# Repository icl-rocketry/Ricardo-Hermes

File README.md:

# Hermes - ICLR Radio Gateway board

ESP32c3 + SX1280 + SKY66112-11 Half-Duplex Lora radio gateway board.

## WIP!

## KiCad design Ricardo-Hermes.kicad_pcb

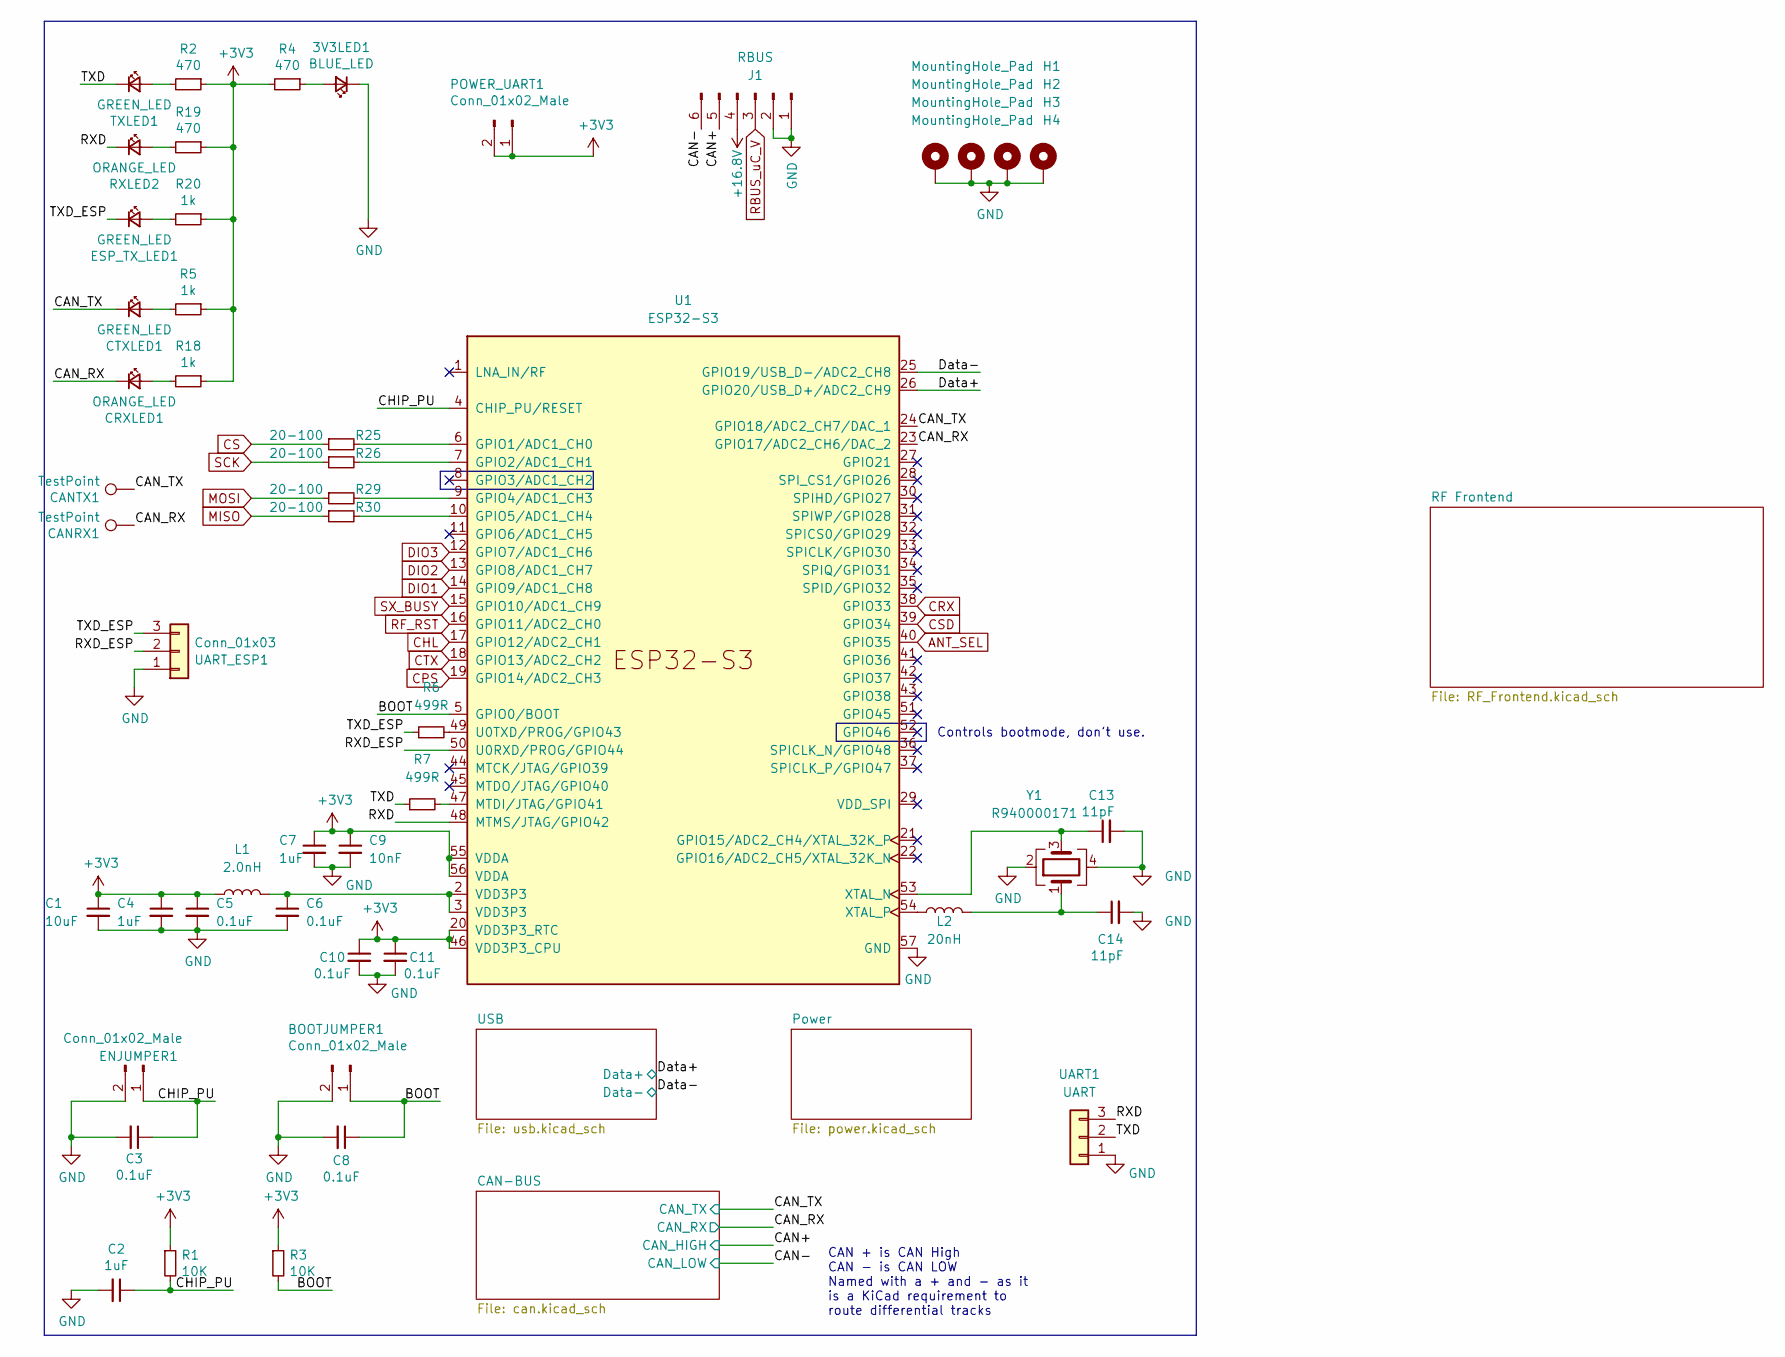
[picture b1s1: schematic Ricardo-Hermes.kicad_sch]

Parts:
3V3LED1: BLUE_LED; D_0402_1005Metric
BOOTJUMPER1: Conn_01x02_Male; PinHeader_1x02_P2.54mm_Vertical
C1: 10uF; C_0402_1005Metric
C2, C4, C7: 1uF; C_0402_1005Metric
C3, C5, C6, C8, C10, C11: 0.1uF; C_0402_1005Metric
C9: 10nF; C_0402_1005Metric
C13, C14: 11pF; C_0402_1005Metric
CANRX1: TestPoint; TestPoint_Pad_D1.0mm
CANTX1: TestPoint; TestPoint_Pad_D1.0mm
CRXLED1: ORANGE_LED; D_0402_1005Metric
CTXLED1: GREEN_LED; D_0402_1005Metric
ENJUMPER1: Conn_01x02_Male; PinHeader_1x02_P2.54mm_Vertical
ESP_TX_LED1: GREEN_LED; D_0402_1005Metric
H1, H2, H3, H4: MountingHole_Pad; MountingHole_3.2mm_M3_DIN965_Pad
J1: RBUS; Molex_Mini-Fit_Jr_5566-06A_2x03_P4.20mm_Vertical
L1: 2.0nH; L_0402_1005Metric
L2: 20nH; L_0402_1005Metric
POWER_UART1: Conn_01x02_Male; PinHeader_1x02_P2.54mm_Vertical
R1, R3: 10K; R_0402_1005Metric
R2, R4, R19: 470; R_0402_1005Metric
R5, R18, R20: 1k; R_0402_1005Metric
R6, R7: 499R; R_0402_1005Metric
R25, R26, R29, R30: 20-100; R_0402_1005Metric
RXLED2: ORANGE_LED; D_0402_1005Metric
TXLED1: GREEN_LED; D_0402_1005Metric
U1: ESP32-S3; QFN40P700X700X90-57N
UART1: UART; Molex_Nano-Fit_105313-xx03_1x03_P2.50mm_Horizontal
UART_ESP1: Conn_01x03; PinHeader_1x03_P2.54mm_Vertical
Y1: R940000171; Crystal_SMD_2016-4Pin_2.0x1.6mm

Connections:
+16.8V: J1.4
/BOOT: BOOTJUMPER1.1, C8.1, R3.2, U1.5 (GPIO0/BOOT)
/CAN+: J1.5; also elsewhere on the board
/CAN-: J1.6; also elsewhere on the board
/CAN_RX: CANRX1.1, CRXLED1.1 (K), U1.23 (GPIO17/ADC2_CH6/DAC_2); also elsewhere on the board
/CAN_TX: CANTX1.1, CTXLED1.1 (K), U1.24 (GPIO18/ADC2_CH7/DAC_1); also elsewhere on the board
/CHIP_PU: C2.1, C3.1, ENJUMPER1.1, R1.2, U1.4 (CHIP_PU/RESET)
/Data+: U1.26 (GPIO20/USB_D+/ADC2_CH9); also elsewhere on the board
/Data-: U1.25 (GPIO19/USB_D-/ADC2_CH8); also elsewhere on the board
/RXD: RXLED2.1 (K), U1.48 (MTMS/JTAG/GPIO42), UART1.3
/RXD_ESP: U1.50 (U0RXD/PROG/GPIO44), UART_ESP1.2
/TXD: R7.1, TXLED1.1 (K), UART1.2
/TXD_ESP: ESP_TX_LED1.1 (K), R6.1, UART_ESP1.3
ANT_SEL: U1.40 (GPIO35); also elsewhere on the board
CHL: U1.17 (GPIO12/ADC2_CH1); also elsewhere on the board
CPS: U1.19 (GPIO14/ADC2_CH3); also elsewhere on the board
CRX: U1.38 (GPIO33); also elsewhere on the board
CS: R25.1; also elsewhere on the board
CSD: U1.39 (GPIO34); also elsewhere on the board
CTX: U1.18 (GPIO13/ADC2_CH2); also elsewhere on the board
DIO1: U1.14 (GPIO9/ADC1_CH8); also elsewhere on the board
DIO2: U1.13 (GPIO8/ADC1_CH7); also elsewhere on the board
DIO3: U1.12 (GPIO7/ADC1_CH6); also elsewhere on the board
GND: 3V3LED1.1 (K), BOOTJUMPER1.2, C1.2, C2.2, C3.2, C4.2, C5.2, C6.2, C7.2, C8.2, C9.2, C10.2, C11.2, C13.2, C14.2, ENJUMPER1.2, H1.1, H2.1, H3.1, H4.1, J1.1, J1.2, U1.57 (GND), UART1.1, UART_ESP1.1, Y1.2, Y1.4; also elsewhere on the board
MISO: R30.1; also elsewhere on the board
MOSI: R29.1; also elsewhere on the board
unnamed: 3V3LED1.2 (A), R4.1
unnamed: C6.1, L1.2, U1.2 (VDD3P3), U1.3 (VDD3P3)
unnamed: C14.1, L2.2, Y1.1
unnamed: CRXLED1.2 (A), R18.2
unnamed: CTXLED1.2 (A), R5.2
unnamed: ESP_TX_LED1.2 (A), R20.2
unnamed: R19.2, RXLED2.2 (A)
unnamed: R2.2, TXLED1.2 (A)
unnamed: R25.2, U1.6 (GPIO1/ADC1_CH0)
unnamed: R26.2, U1.7 (GPIO2/ADC1_CH1)
unnamed: R29.2, U1.9 (GPIO4/ADC1_CH3)
unnamed: R30.2, U1.10 (GPIO5/ADC1_CH4)
unnamed: R7.2, U1.47 (MTDI/JTAG/GPIO41)
unnamed: R6.2, U1.49 (U0TXD/PROG/GPIO43)
unnamed: C13.1, U1.53 (XTAL_N), Y1.3
unnamed: L2.1, U1.54 (XTAL_P)
RBUS_uC_V: J1.3; also elsewhere on the board
RF_RST: U1.16 (GPIO11/ADC2_CH0); also elsewhere on the board
SCK: R26.1; also elsewhere on the board
SX_BUSY: U1.15 (GPIO10/ADC1_CH9); also elsewhere on the board

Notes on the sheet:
Controls bootmode, don't use.
CAN + is CAN High CAN - is CAN LOW Named with a + and - as it is a KiCad requirement to route differential tracks

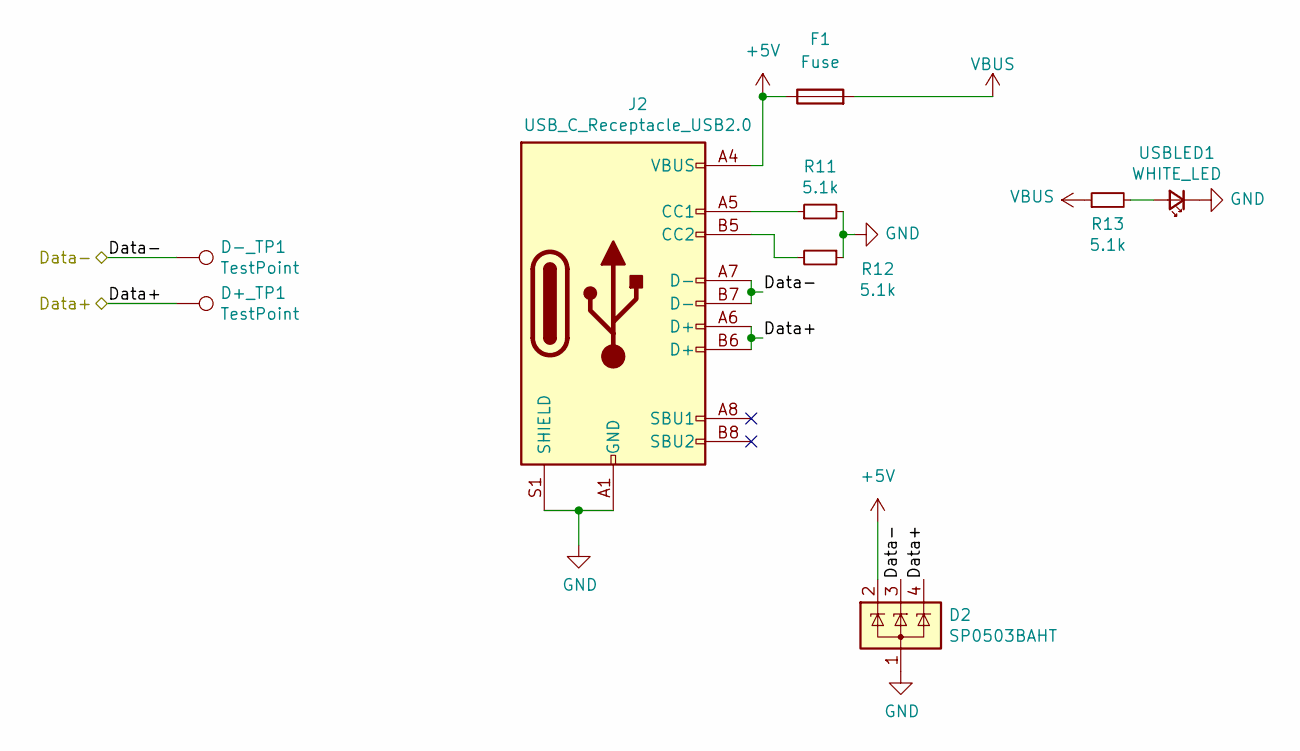
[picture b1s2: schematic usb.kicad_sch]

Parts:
D2: SP0503BAHT; SOT-143
D+_TP1: TestPoint; TestPoint_Pad_D1.0mm
D-_TP1: TestPoint; TestPoint_Pad_D1.0mm
F1: Fuse; Fuse_0603_1608Metric
J2: USB_C_Receptacle_USB2.0; USB_C_Receptacle_Palconn_UTC16-G
R11, R12, R13: 5.1k; R_0402_1005Metric
USBLED1: WHITE_LED; D_0402_1005Metric

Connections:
+5V: D2.2 (K), F1.1, J2.A4 (VBUS), J2.A9 (VBUS), J2.B4 (VBUS), J2.B9 (VBUS)
/Data+: D2.4 (K), D+_TP1.1, J2.A6 (D+), J2.B6 (D+); also elsewhere on the board
/Data-: D2.3 (K), D-_TP1.1, J2.A7 (D-), J2.B7 (D-); also elsewhere on the board
GND: D2.1 (A), J2.A1 (GND), J2.A12 (GND), J2.B1 (GND), J2.B12 (GND), J2.S1 (SHIELD), R11.2, R12.1, USBLED1.1 (K); also elsewhere on the board
unnamed: J2.A5 (CC1), R11.1
unnamed: J2.B5 (CC2), R12.2
unnamed: R13.2, USBLED1.2 (A)
VBUS: F1.2, R13.1; also elsewhere on the board

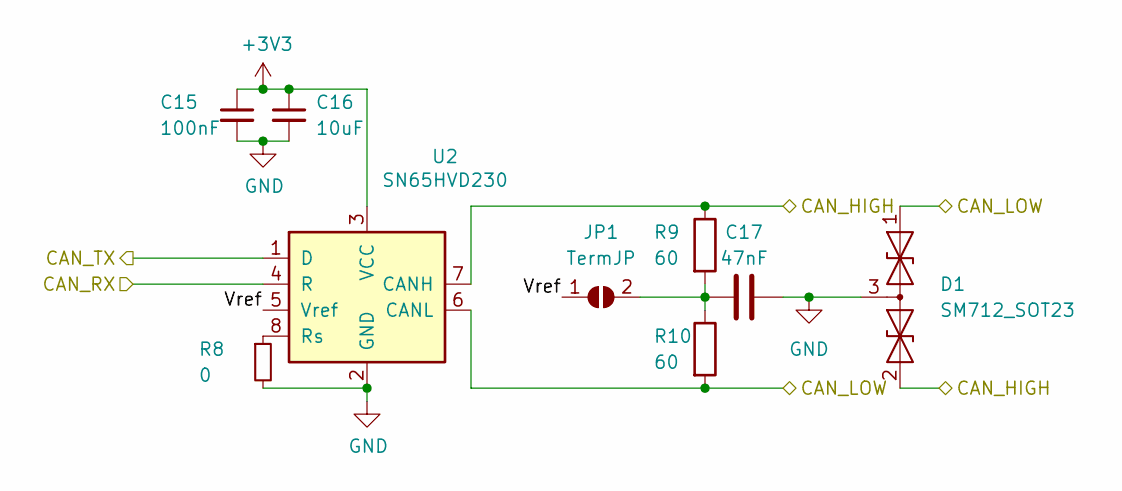
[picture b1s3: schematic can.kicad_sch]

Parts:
C15: 100nF; C_0402_1005Metric
C16: 10uF; C_0402_1005Metric
C17: 47nF; C_0402_1005Metric
D1: SM712_SOT23; SOT-23
JP1: TermJP; SolderJumper-2_P1.3mm_Open_RoundedPad1.0x1.5mm
R8: 0; R_0603_1608Metric
R9, R10: 60; R_0603_1608Metric
U2: SN65HVD230; SOIC-8_3.9x4.9mm_P1.27mm

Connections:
/CAN+: D1.2 (A2), R9.1, U2.7 (CANH); also elsewhere on the board
/CAN-: D1.1 (A1), R10.2, U2.6 (CANL); also elsewhere on the board
/CAN-BUS/Vref: JP1.1 (A), U2.5 (Vref)
/CAN_RX: U2.4 (R); also elsewhere on the board
/CAN_TX: U2.1 (D); also elsewhere on the board
GND: C15.2, C16.2, C17.2, D1.3 (common), R8.2, U2.2 (GND); also elsewhere on the board
unnamed: C17.1, JP1.2 (B), R9.2, R10.1
unnamed: R8.1, U2.8 (Rs)

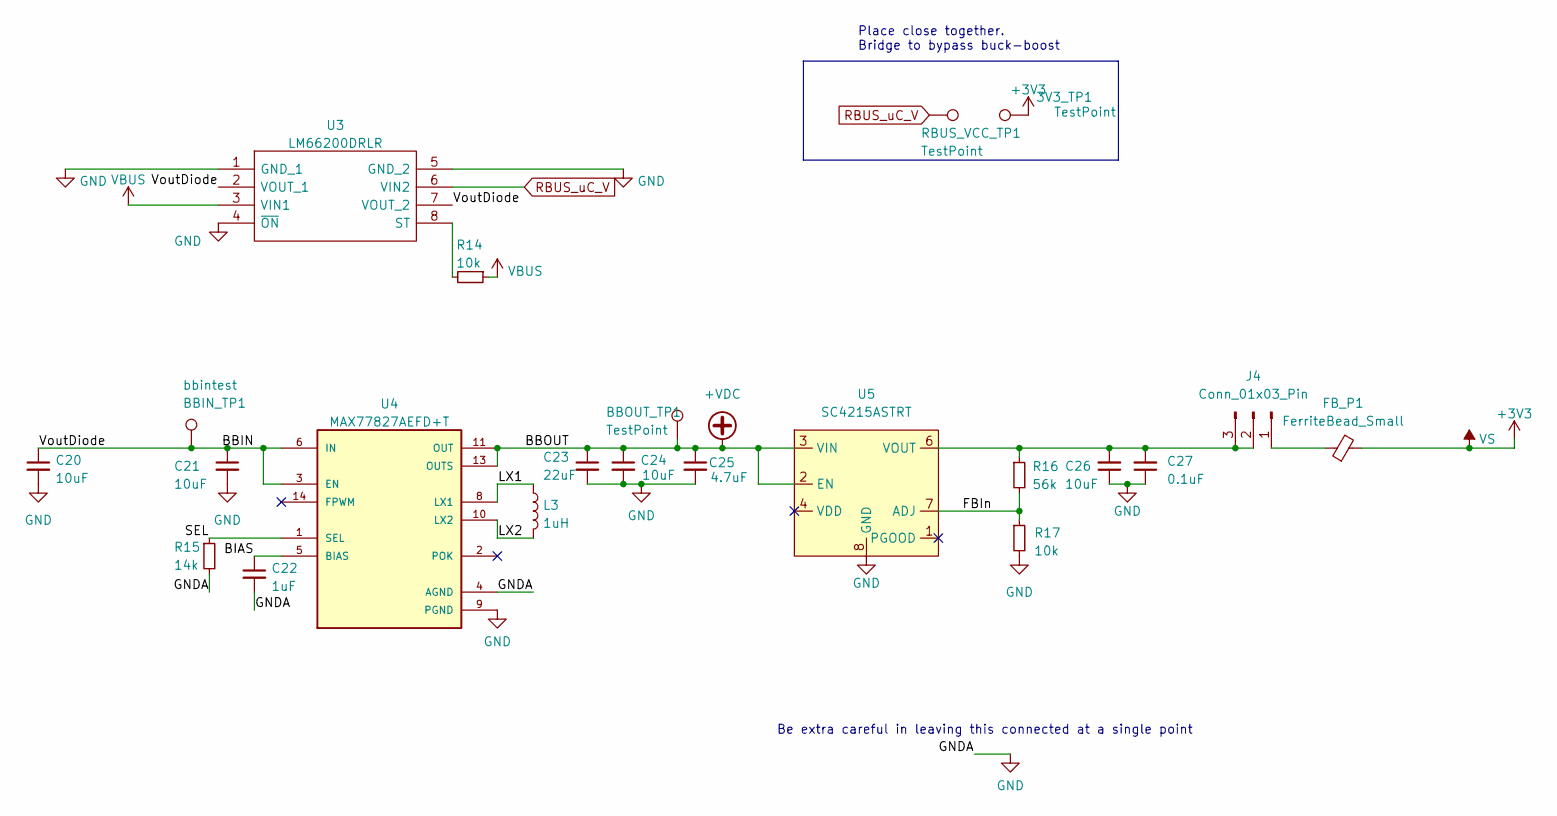
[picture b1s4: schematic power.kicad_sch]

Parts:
3V3_TP1: TestPoint; TestPoint_Pad_D1.5mm
BBIN_TP1: bbintest; TestPoint_Pad_D1.5mm
BBOUT_TP1: TestPoint; TestPoint_Pad_D1.5mm
C20, C24, C26: 10uF; C_0402_1005Metric
C21: 10uF; C_0603_1608Metric
C22: 1uF; C_0402_1005Metric
C23: 22uF; C_0603_1608Metric
C25: 4.7uF; C_0402_1005Metric
C27: 0.1uF; C_0402_1005Metric
FB_P1: FerriteBead_Small; L_0603_1608Metric
J4: Conn_01x03_Pin; PinHeader_1x03_P2.54mm_Vertical
L3: 1uH; L_0805_2012Metric
R14, R17: 10k; R_0402_1005Metric
R15: 14k; R_0402_1005Metric
R16: 56k; R_0402_1005Metric
RBUS_VCC_TP1: TestPoint; TestPoint_Pad_D1.5mm
U3: LM66200DRLR; SOTFL50P160X60-8N; Manufacturer_Part_Number LM66200DRLR; Mouser Part Number 595-LM66200DRLR
U4: MAX77827AEFD+T; CONV_MAX77827AEFD+T; PARTREV B
U5: SC4215ASTRT; SOIC127P599X175-9N

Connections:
+VDC: BBOUT_TP1.1, C23.1, C24.1, C25.1, U4.11 (OUT), U4.13 (OUTS), U5.2 (EN), U5.3 (VIN)
/Power/BBIN: BBIN_TP1.1, C20.1, C21.1, U3.2 (VOUT_1), U3.7 (VOUT_2), U4.3 (EN), U4.6 (IN)
/Power/BIAS: C22.1, U4.5 (BIAS)
/Power/FBIn: R16.2, R17.1, U5.7 (ADJ)
/Power/LX1: L3.1, U4.8 (LX1)
/Power/LX2: L3.2, U4.10 (LX2)
/Power/SEL: R15.1, U4.1 (SEL)
GND: C20.2, C21.2, C22.2, C23.2, C24.2, C25.2, C26.1, C27.1, R15.2, R17.2, U3.1 (GND_1), U3.4 (~ON), U3.5 (GND_2), U4.4 (AGND), U4.9 (PGND), U5.8 (GND), U5.9 (GND); also elsewhere on the board
unnamed: R14.2, U3.8 (ST)
RBUS_uC_V: RBUS_VCC_TP1.1, U3.6 (VIN2); also elsewhere on the board
VBUS: R14.1, U3.3 (VIN1); also elsewhere on the board

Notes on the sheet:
Place close together. Bridge to bypass buck-boost
Be extra careful in leaving this connected at a single point

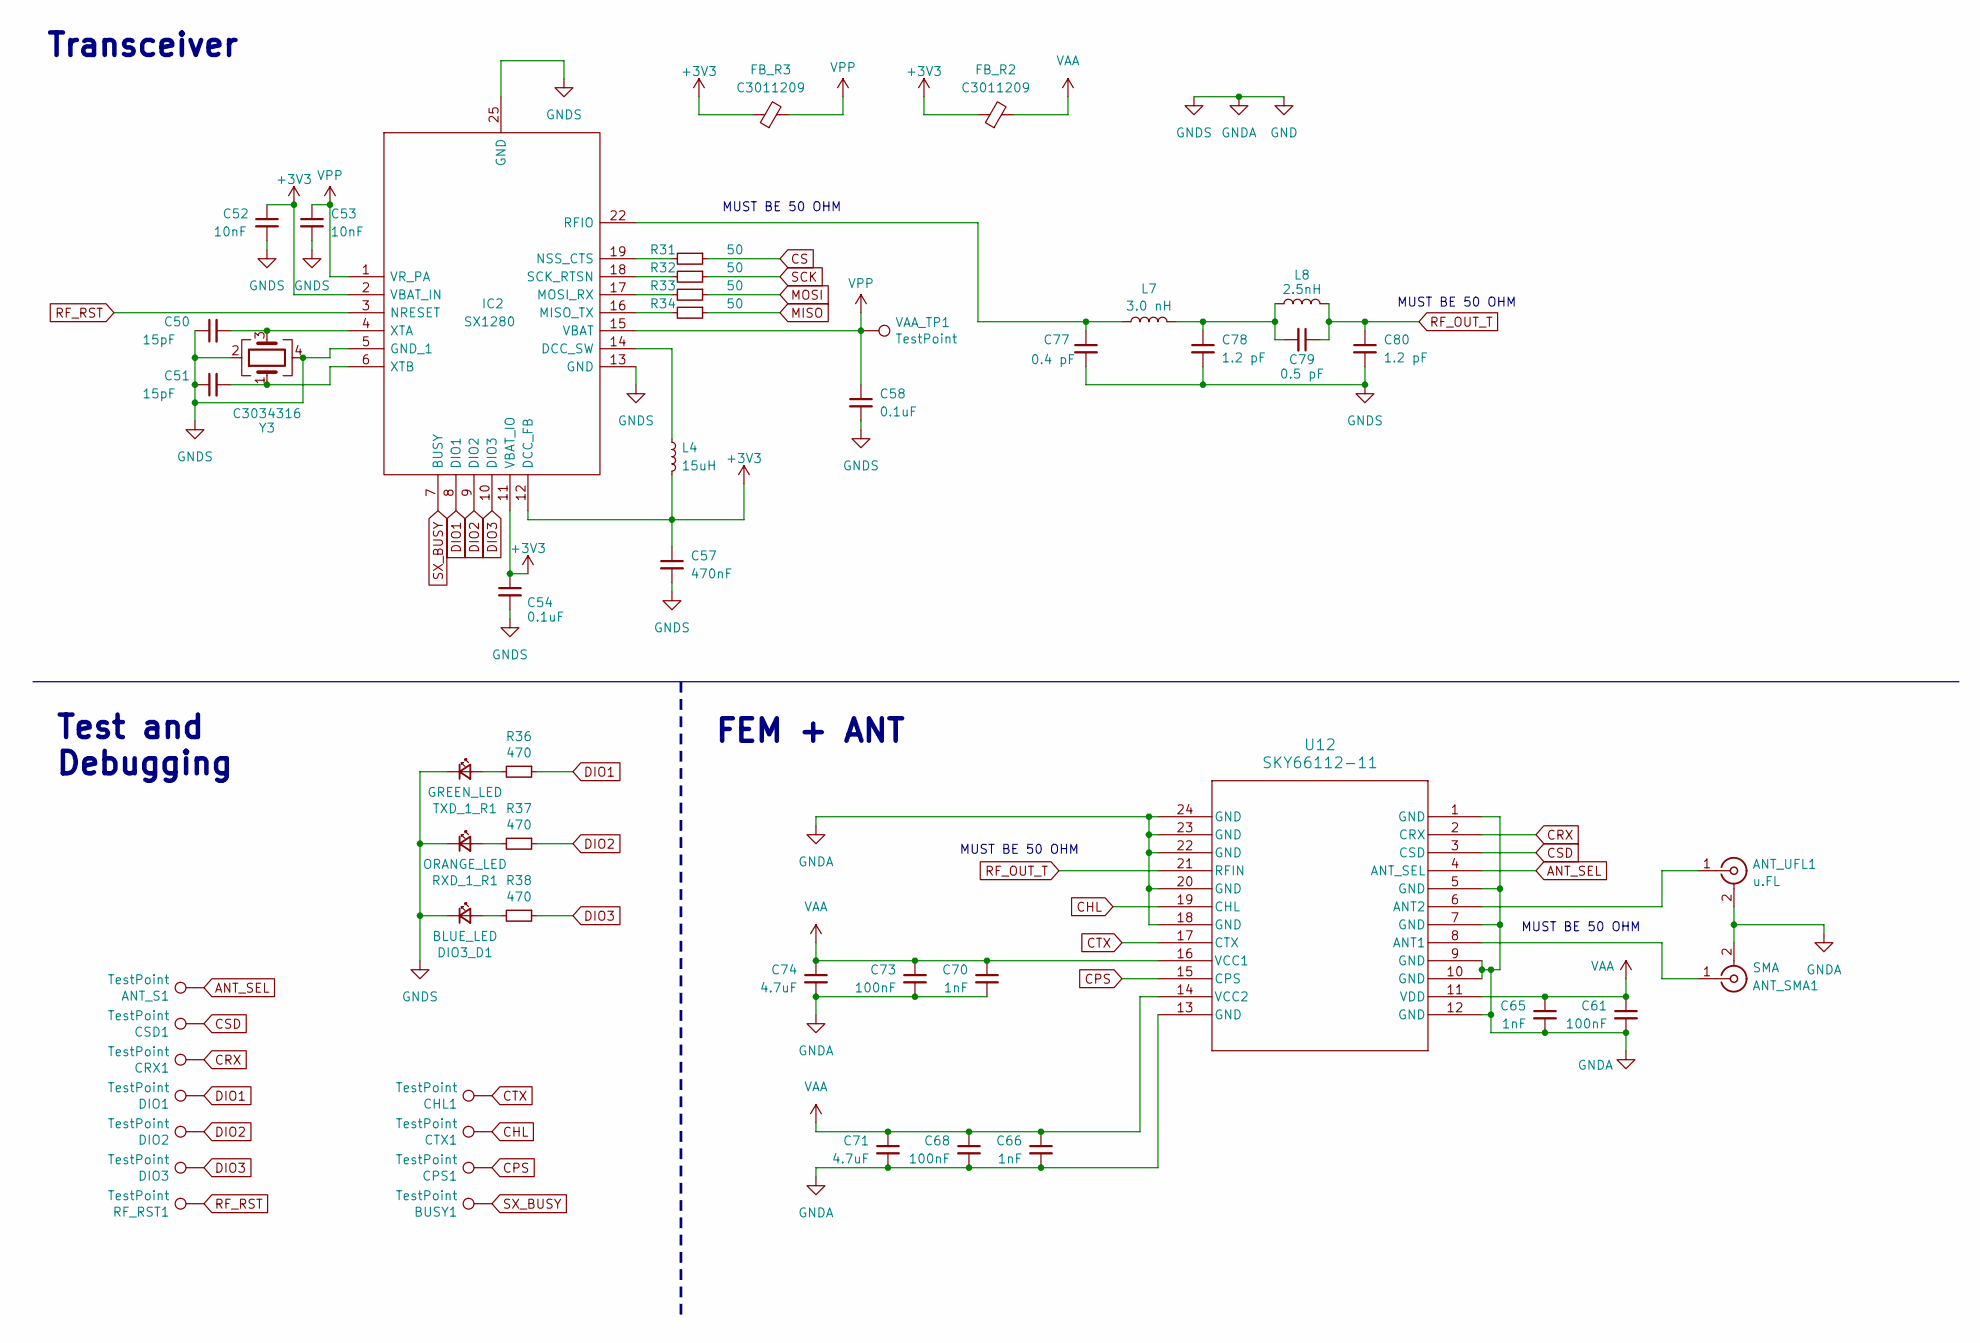
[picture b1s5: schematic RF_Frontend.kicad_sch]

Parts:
ANT_S1: TestPoint; TestPoint_Pad_D1.0mm
ANT_SMA1: SMA; SMA_Molex_73251-1153_EdgeMount_Horizontal
ANT_UFL1: u.FL; U.FL_Hirose_U.FL-R-SMT-1_Vertical
BUSY1: TestPoint; TestPoint_Pad_D1.0mm
C50, C51: 15pF; C_0402_1005Metric
C52, C53: 10nF; C_0402_1005Metric
C54, C58: 0.1uF; C_0402_1005Metric
C57: 470nF; C_0402_1005Metric
C61, C68, C73: 100nF; C_0402_1005Metric
C65, C66, C70: 1nF; C_0402_1005Metric
C71, C74: 4.7uF; C_0603_1608Metric
C77: 0.4 pF; C_0402_1005Metric
C78, C80: 1.2 pF; C_0402_1005Metric
C79: 0.5 pF; C_0402_1005Metric
CHL1: TestPoint; TestPoint_Pad_D1.0mm
CPS1: TestPoint; TestPoint_Pad_D1.0mm
CRX1: TestPoint; TestPoint_Pad_D1.0mm
CSD1: TestPoint; TestPoint_Pad_D1.0mm
CTX1: TestPoint; TestPoint_Pad_D1.0mm
DIO1, DIO2, DIO3: TestPoint; TestPoint_Pad_D1.0mm
DIO3_D1: BLUE_LED; D_0402_1005Metric
FB_R2, FB_R3: C3011209; L_0603_1608Metric
IC2: SX1280; QFN50P400X400X95-24N; Manufacturer_Part_Number SX1280IMLTRT; Mouser Part Number 947-SX1280IMLTRT
L4: 15uH; L_0603_1608Metric
L7: 3.0 nH; L_0402_1005Metric
L8: 2.5nH; L_0402_1005Metric
R31, R32, R33, R34: 50; R_0402_1005Metric
R36, R37, R38: 470; R_0402_1005Metric
RF_RST1: TestPoint; TestPoint_Pad_D1.0mm
RXD_1_R1: ORANGE_LED; D_0402_1005Metric
TXD_1_R1: GREEN_LED; D_0402_1005Metric
U12: SKY66112-11; SKY66112-11_SKY
VAA_TP1: TestPoint; TestPoint_Pad_D1.0mm
Y3: C3034316; Crystal_SMD_2016-4Pin_2.0x1.6mm

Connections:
ANT_SEL: ANT_S1.1, U12.4 (ANT_SEL); also elsewhere on the board
CHL: CTX1.1, U12.19 (CHL); also elsewhere on the board
CPS: CPS1.1, U12.15 (CPS); also elsewhere on the board
CRX: CRX1.1, U12.2 (CRX); also elsewhere on the board
CS: R31.1; also elsewhere on the board
CSD: CSD1.1, U12.3 (CSD); also elsewhere on the board
CTX: CHL1.1, U12.17 (CTX); also elsewhere on the board
DIO1: DIO1.1, IC2.8 (DIO1), R36.1; also elsewhere on the board
DIO2: DIO2.1, IC2.9 (DIO2), R37.1; also elsewhere on the board
DIO3: DIO3.1, IC2.10 (DIO3), R38.1; also elsewhere on the board
GND: ANT_SMA1.2 (Ext), ANT_UFL1.2 (Ext), C50.1, C51.1, C52.2, C53.2, C54.2, C57.2, C58.2, C61.2, C65.2, C66.2, C68.2, C70.2, C71.2, C73.2, C74.2, C77.2, C78.2, C80.2, DIO3_D1.1 (K), IC2.5 (GND_1), IC2.13 (GND), IC2.20 (GND), IC2.21 (GND), IC2.23 (GND), IC2.24 (GND), IC2.25 (GND), RXD_1_R1.1 (K), TXD_1_R1.1 (K), U12.1 (GND), U12.5 (GND), U12.7 (GND), U12.9 (GND), U12.10 (GND), U12.12 (GND), U12.13 (GND), U12.18 (GND), U12.20 (GND), U12.22 (GND), U12.23 (GND), U12.24 (GND), Y3.2, Y3.4; also elsewhere on the board
MISO: R34.1; also elsewhere on the board
MOSI: R33.1; also elsewhere on the board
unnamed: ANT_SMA1.1 (In), U12.8 (ANT1)
unnamed: ANT_UFL1.1 (In), U12.6 (ANT2)
unnamed: C78.1, C79.2, L7.2, L8.1
unnamed: DIO3_D1.2 (A), R38.2
unnamed: IC2.16 (MISO_TX), R34.2
unnamed: IC2.17 (MOSI_RX), R33.2
unnamed: IC2.19 (NSS_CTS), R31.2
unnamed: C77.1, IC2.22 (RFIO), L7.1
unnamed: IC2.18 (SCK_RTSN), R32.2
unnamed: C50.2, IC2.4 (XTA), Y3.3
unnamed: C51.2, IC2.6 (XTB), Y3.1
unnamed: IC2.14 (DCC_SW), L4.1
unnamed: R37.2, RXD_1_R1.2 (A)
unnamed: R36.2, TXD_1_R1.2 (A)
RF_OUT_T: C79.1, C80.1, L8.2, U12.21 (RFIN)
RF_RST: IC2.3 (NRESET), RF_RST1.1; also elsewhere on the board
SCK: R32.1; also elsewhere on the board
SX_BUSY: BUSY1.1, IC2.7 (BUSY); also elsewhere on the board
VAA: C61.1, C65.1, C66.1, C68.1, C70.1, C71.1, C73.1, C74.1, FB_R2.2, U12.11 (VDD), U12.14 (VCC2), U12.16 (VCC1)

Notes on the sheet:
MUST BE 50 OHM
Transceiver
Test and Debugging
FEM + ANT

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
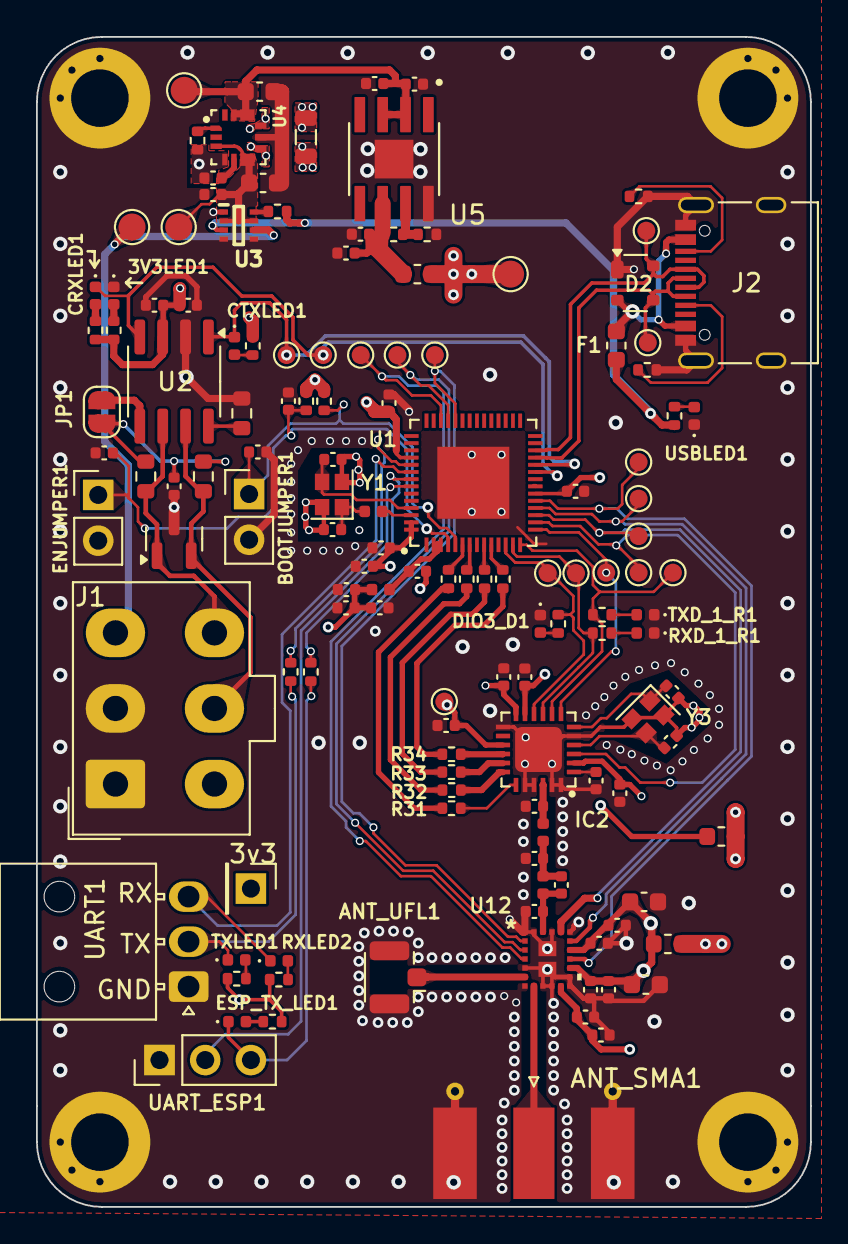
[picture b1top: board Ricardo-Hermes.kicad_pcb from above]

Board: 4 copper layers, 43.0 x 65.0 mm, 138 parts (0 on the bottom side), 81 nets.

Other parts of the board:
3v3: Conn_01x02_Male; PinHeader_1x01_P2.54mm_Vertical

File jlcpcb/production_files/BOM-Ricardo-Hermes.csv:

Comment,Designator,Footprint,LCSC,Quantity
MAX77827AEFD+T,U4,CONV_MAX77827AEFD+T,C1020009,1
1uH,L3,L_0805_2012Metric,C113100,1
470,"R2,R36,R37,R38,R4",R_0402_1005Metric,C114877,5
1k,"R18,R20,R5",R_0402_1005Metric,C11702,3
SN65HVD230,U2,SOIC-8_3.9x4.9mm_P1.27mm,C12084,1
SX1280,IC2,QFN50P400X400X95-24N,C125969,1
ORANGE_LED,CRXLED1,D_0402_1005Metric,C130720,1
GREEN_LED,CTXLED1,D_0402_1005Metric,C130722,1
BLUE_LED,"3V3LED1,DIO3_D1",D_0402_1005Metric,C130724,2
WHITE_LED,USBLED1,D_0402_1005Metric,C130725,1
Fuse,F1,Fuse_0603_1608Metric,C135323,1
499R,"R6,R7",R_0402_1005Metric,C137970,2
1nF,"C65,C66,C70",C_0402_1005Metric,C14442,3
1uF,"C2,C22,C4,C7",C_0402_1005Metric,C14445,4
10nF,"C52,C53,C9",C_0402_1005Metric,C15195,3
15uH,L4,L_0603_1608Metric,C18221256,1
4.7uF,"C71,C74",C_0603_1608Metric,C19666,2
470,R19,R_0402_1005Metric,C25117,1
0,R8,R_0603_1608Metric,C253507,1
10k,"R14,R17",R_0402_1005Metric,C25744,2
56k,R16,R_0402_1005Metric,C25796,1
5.1k,"R11,R12,R13",R_0402_1005Metric,C25905,3
SKY66112-11,U12,SKY66112-11_SKY,C2654460,1
3.0 nH,L7,L_0402_1005Metric,C275284,1
ESP32-S3,U1,QFN40P700X700X90-57N,C2913192,1
USB_C_Receptacle_USB2.0,J2,USB_C_Receptacle_Palconn_UTC16-G,C2988369,1
FerriteBead_Small,"FB_P1,FB_R2,FB_R3",L_0603_1608Metric,C3011209,3
C3034316,Y3,Crystal_SMD_2016-4Pin_2.0x1.6mm,C3034316,1
2.5nH,L8,L_0402_1005Metric,C317668,1
20nH,L2,L_0402_1005Metric,C317958,1
LM66200DRLR,U3,SOTFL50P160X60-8N,C3235556,1
SC4215ASTRT,U5,SOIC127P599X175-9N,C353859,1
15pF,C50,C_0402_1005Metric,C441742,1
470nF,C57,C_0402_1005Metric,C47339,1
SM712_SOT23,D1,SOT-23,C502564,1
14k,R15,R_0402_1005Metric,C54831,1
4.7uF,C25,C_0402_1005Metric,C5718982,1
22uF,C23,C_0603_1608Metric,C60077,1
10K,"R1,R3",R_0402_1005Metric,C60490,2
SP0503BAHT,D2,SOT-143,C7074,1
11pF,"C13,C14",C_0402_1005Metric,C710643,2
R940000171,Y1,Crystal_SMD_2016-4Pin_2.0x1.6mm,C7420784,1
2.0nH,L1,L_0402_1005Metric,C76769,1
1.2 pF,"C78,C80",C_0402_1005Metric,C76899,2
0.5 pF,C79,C_0402_1005Metric,C76911,1
15pF,C51,C_0402_1005Metric,C76950,1
10uF,"C1,C16,C20,C24,C26",C_0402_1005Metric,C77000,5
47nF,C17,C_0402_1005Metric,C77012,1
0.1uF,"C10,C11,C15,C27,C3,C5,C54,C58,C6,C61,C68,C73,C8",C_0402_1005Metric,C77020,13
20-100,"R25,R26,R29,R30,R31,R32,R33,R34",R_0402_1005Metric,C853312,8
10uF,C21,C_0603_1608Metric,C86275,1
u.FL,ANT_UFL1,U.FL_Hirose_U.FL-R-SMT-1_Vertical,C88374,1
0.4 pF,C77,C_0402_1005Metric,C88900,1
TestPoint,RF_RST1,TestPoint_Pad_D1.0mm,,1
RBUS,J1,Molex_Mini-Fit_Jr_5566-06A_2x03_P4.20mm_Vertical,,1
bbintest,BBIN_TP1,TestPoint_Pad_D1.5mm,,1
TestPoint,CRX1,TestPoint_Pad_D1.0mm,,1
60,R9,R_0603_1608Metric,,1
TestPoint,CSD1,TestPoint_Pad_D1.0mm,,1
TestPoint,CANRX1,TestPoint_Pad_D1.0mm,,1
TestPoint,DIO3,TestPoint_Pad_D1.0mm,,1
TestPoint,VAA_TP1,TestPoint_Pad_D1.0mm,,1
TestPoint,CTX1,TestPoint_Pad_D1.0mm,,1
SMA,ANT_SMA1,SMA_Molex_73251-1153_EdgeMount_Horizontal,,1
TermJP,JP1,SolderJumper-2_P1.3mm_Open_RoundedPad1.0x1.5mm,,1
TestPoint,CPS1,TestPoint_Pad_D1.0mm,,1
TestPoint,3V3_TP1,TestPoint_Pad_D1.5mm,,1
MountingHole_Pad,H3,MountingHole_3.2mm_M3_DIN965_Pad,,1
TestPoint,RBUS_VCC_TP1,TestPoint_Pad_D1.5mm,,1
TestPoint,BBOUT_TP1,TestPoint_Pad_D1.5mm,,1
UART,UART1,Molex_Nano-Fit_105313-xx03_1x03_P2.50mm_Horizontal,,1
TestPoint,CHL1,TestPoint_Pad_D1.0mm,,1
MountingHole_Pad,H1,MountingHole_3.2mm_M3_DIN965_Pad,,1
MountingHole_Pad,H4,MountingHole_3.2mm_M3_DIN965_Pad,,1
TestPoint,DIO1,TestPoint_Pad_D1.0mm,,1
Conn_01x02_Male,ENJUMPER1,PinHeader_1x02_P2.54mm_Vertical,,1
TestPoint,BUSY1,TestPoint_Pad_D1.0mm,,1
Conn_01x02_Male,BOOTJUMPER1,PinHeader_1x02_P2.54mm_Vertical,,1
TestPoint,ANT_S1,TestPoint_Pad_D1.0mm,,1
TestPoint,DIO2,TestPoint_Pad_D1.0mm,,1
TestPoint,CANTX1,TestPoint_Pad_D1.0mm,,1
MountingHole_Pad,H2,MountingHole_3.2mm_M3_DIN965_Pad,,1
60,R10,R_0603_1608Metric,,1
Conn_01x03,UART_ESP1,PinHeader_1x03_P2.54mm_Vertical,,1
Conn_01x02_Male,3v3,PinHeader_1x01_P2.54mm_Vertical,,1

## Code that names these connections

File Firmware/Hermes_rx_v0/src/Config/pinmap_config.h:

/*
**********************
* PINS               *
**********************
*/
#pragma once

namespace PinMap
{

    static constexpr int H_MISO = 12;
    static constexpr int H_MOSI = 13;
    static constexpr int H_SCLK = 14;

    static constexpr int MagCs = 15;
    static constexpr int ImuCs_1 = 16;
    static constexpr int ImuCs_2 = 17;

    // static constexpr int V_SCLK = 18;
    // static constexpr int V_MISO = 19;
    static constexpr int _SDA = 21;
    static constexpr int _SCL = 22;
    // static constexpr int V_MOSI = 23;

    static constexpr int V_SCLK = 37;
    static constexpr int V_MISO = 38;
    static constexpr int V_MOSI = 36;
    static constexpr int sdcs = 4;

    // static constexpr int SdCs_1 = 25;
    // static constexpr int SdCs_2 = 26;
    // static constexpr int Buzzer = 27;

    static constexpr int TxCan = 32;
    static constexpr int RxCan = 33;

    // AMP

    /*
    Pin means amp pin itself
     Mode | Description               | CSD (Pin 3) | CPS (Pin 15) | CRX (Pin 2) | CTX (Pin 17) | CHL (Pin 19)
     -----+---------------------------+-------------+--------------+-------------+--------------+-------------
     0    | All off (sleep mode)      | 0           | X            | X           | X            | X
     1    | Receive LNA mode          | 1           | 0            | 1           | 0            | X
     2    | Transmit high-power mode  | 1           | 0            | X           | 1            | 1
     3    | Transmit low-power mode   | 1           | 0            | X           | 1            | 0
     4    | Receive bypass mode       | 1           | 1            | 1           | 0            | X
     5    | Transmit bypass mode      | 1           | 1            | X           | 1            | X
     6    | All off (sleep mode)      | 1           | X            | 0           | 0            | X
    */
    static constexpr int AMP_ANT_SEL = 35; // 0 is SMA, 1 is UFL
    static constexpr int AMP_CSD = 34;     // AMP off (sleeping) -> 0, AMP on -> 1
    static constexpr int AMP_CRX = 33;     // Enable RX
    static constexpr int AMP_CHL = 17;     // high power TX -> 1, Low power TX -> 0
    static constexpr int AMP_CTX = 13;     // Enable TX
    static constexpr int AMP_CPS = 14;     // Bypass mode

    // SX1280
    static constexpr int SPI_SX1280_CS = 1;
    static constexpr int SPI_SX1280_SCK = 2;
    static constexpr int SPI_SX1280_MOSI = 4;
    static constexpr int SPI_SX1280_MISO = 5;
    static constexpr int SX1280_DIO1 = 9; // txd led
    static constexpr int SX1280_DIO2 = 8; // rxd led
    static constexpr int SX1280_DIO3 = 7;
    static constexpr int SX1280_BUSY = 10;
    static constexpr int SX1280_RST = 11;

    // UART
    static constexpr int TXD_ESP_UART = 43;
    static constexpr int RXD_ESP_UART = 44;
    static constexpr int TXD_UART = 41;
    static constexpr int RXD_UART = 42;

    // Pickle
    static constexpr int LoraReset = 11;
    static constexpr int LoraCs = 1;
    // might switch to busy, who knows lol
    static constexpr int LoraInt = 9;
    // static constexpr int TxCan = 27;
    // static constexpr int RxCan = 14;

    // static constexpr int TxCan = 33;
    // static constexpr int RxCan = 32;
    // static constexpr int SdDet_1 = 34;
    // static constexpr int SdDet_2 = 35;
    // static constexpr int BattVolt = 36;
    // static constexpr int LoraInt = 39;
};

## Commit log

2024-11-24 Alpha revision
2024-11-24 Fixed library assignment
2024-11-25 Added Faraday cage around PCB edge
    Less emi more betterer
2024-11-25 Changed UART connector
    Now with 1000% more nanofit!
2024-11-25 Changed uart conn
    Get transposed!
2024-11-25 :D
    :D
2024-11-26 Changed via stitching
2024-11-27 Minor improvements
2024-11-28 Fixed Libraries
2024-11-28 Minor changes
2024-12-09 Post review changes WIP
2024-12-09 Fixed minor issues
2024-12-10 Minor fixes
2024-12-15 Silkscreen WIP
2024-12-18 Final changes
    Art and BOM still need to be done
2024-12-31 Silkscreen changes
2025-01-21 Post Review changes, more to come...
2025-01-22 Tidying up
2025-03-06 Finishing touches without BOM
2025-04-17 finishing changes
2025-04-23 Auto stash before merge of "main" and "origin/main"
2025-04-23 Prod Files
2025-04-23 Final manu files
    Needs to be looked over
2025-04-24 Minor fix
2025-04-24 Interleaved saves issue
2025-04-24 Went for a 3v3 plane
2025-04-25 Final changes and splitter prod files
    splitter repo tbd
2025-04-25 New leds
2025-04-25 Final fixes
2025-04-26 qr code
2025-05-08 Forgot to push this silkscreen change
2025-05-16 Firmware
    qq
2025-05-16 firmware2
2025-06-14 PCB status: unfucked
    + sick art
2025-06-14 added 3d
2025-07-16 Range test firmware + folder structure
    :)
